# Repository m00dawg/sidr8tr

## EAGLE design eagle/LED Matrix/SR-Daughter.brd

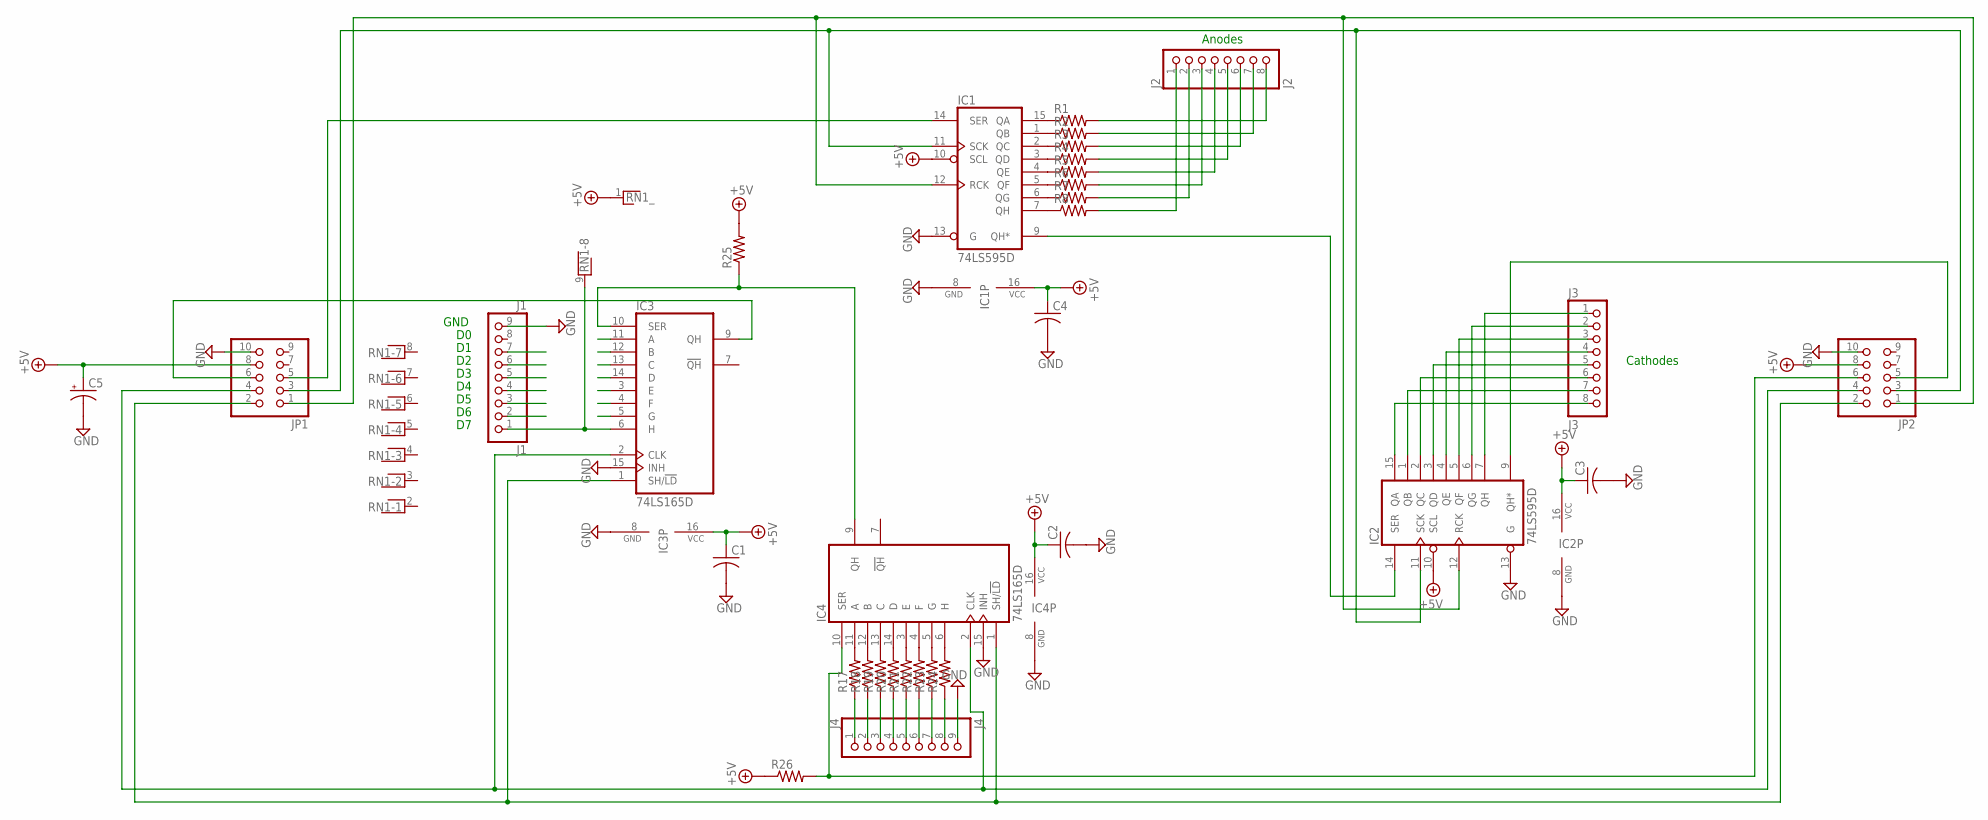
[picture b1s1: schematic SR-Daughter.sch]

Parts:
C1, C2, C3, C4: C-USC0603; C0603
C5: CPOL-USE2-5; E2-5
IC1, IC2: 74LS595D; SO16
IC3, IC4: 74LS165D; SO16
J1: J1; 1X09
J2: J2; 1X08
J3: J3; 1X08
J4: J4; 1X09
JP1, JP2: PINHD-2X5; 2X05
R1, R2, R3, R4, R5, R6, R7, R8, R17, R18, R19, R20, R21, R22, R23, R24, R25, R26: R-US_M0805; M0805
RN1: RNX8; RN-9

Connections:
+5V: C1.1, C2.1, C3.1, C4.1, C5.+, IC1.10 (SCL), IC1.16 (VCC), IC2.10 (SCL), IC2.16 (VCC), IC3.16 (VCC), IC4.16 (VCC), JP1.8, JP2.8, R25.2, R26.1, RN1.1
CLK0: IC3.2 (CLK), IC4.2 (CLK), JP1.4, JP2.4
CLK1: IC3.1 (SH/!LD), IC4.1 (SH/!LD), JP1.2, JP2.2
GND: C1.2, C2.2, C3.2, C4.2, C5.-, IC1.8 (GND), IC1.13 (G), IC2.8 (GND), IC2.13 (G), IC3.8 (GND), IC3.15 (INH), IC4.8 (GND), IC4.15 (INH), J1.9, J4.9, JP1.10, JP2.10
unnamed: IC1.15 (QA), R1.1
unnamed: IC1.1 (QB), R2.1
unnamed: IC1.2 (QC), R3.1
unnamed: IC1.3 (QD), R4.1
unnamed: IC1.4 (QE), R5.1
unnamed: IC1.5 (QF), R6.1
unnamed: IC1.6 (QG), R7.1
unnamed: IC1.7 (QH), R8.1
unnamed: J2.1, R8.2
unnamed: J2.2, R7.2
unnamed: J2.3, R6.2
unnamed: J2.4, R5.2
unnamed: J2.5, R4.2
unnamed: J2.6, R3.2
unnamed: J2.7, R2.2
unnamed: IC3.6 (H), J1.1, RN1.9
unnamed: IC4.11 (A), R17.2
unnamed: IC4.12 (B), R18.2
unnamed: J2.8, R1.2
unnamed: IC2.15 (QA), J3.8
unnamed: IC2.1 (QB), J3.7
unnamed: IC2.2 (QC), J3.6
unnamed: IC2.3 (QD), J3.5
unnamed: IC2.4 (QE), J3.4
unnamed: IC4.13 (C), R19.2
unnamed: IC4.14 (D), R20.2
unnamed: IC2.5 (QF), J3.3
unnamed: IC4.3 (E), R21.2
unnamed: IC4.4 (F), R22.2
unnamed: IC4.5 (G), R23.2
unnamed: IC2.6 (QG), J3.2
unnamed: IC2.7 (QH), J3.1
unnamed: J4.1, R17.1
unnamed: J4.2, R18.1
unnamed: J4.3, R19.1
unnamed: J4.4, R20.1
unnamed: J4.5, R21.1
unnamed: J4.6, R22.1
unnamed: J4.7, R23.1
unnamed: IC4.6 (H), R24.2
unnamed: J4.8, R24.1
unnamed: IC3.9 (QH), JP1.6
unnamed: IC3.10 (SER), IC4.9 (QH), R25.1
unnamed: IC4.10 (SER), JP2.6, R26.2
unnamed: IC1.14 (SER), JP1.5
unnamed: IC1.9 (QH*), IC2.14 (SER)
unnamed: IC2.9 (QH*), JP2.5
unnamed: IC1.12 (RCK), IC2.12 (RCK), JP1.1, JP2.1
unnamed: IC1.11 (SCK), IC2.11 (SCK), JP1.3, JP2.3

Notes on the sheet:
GND
Anodes
Cathodes

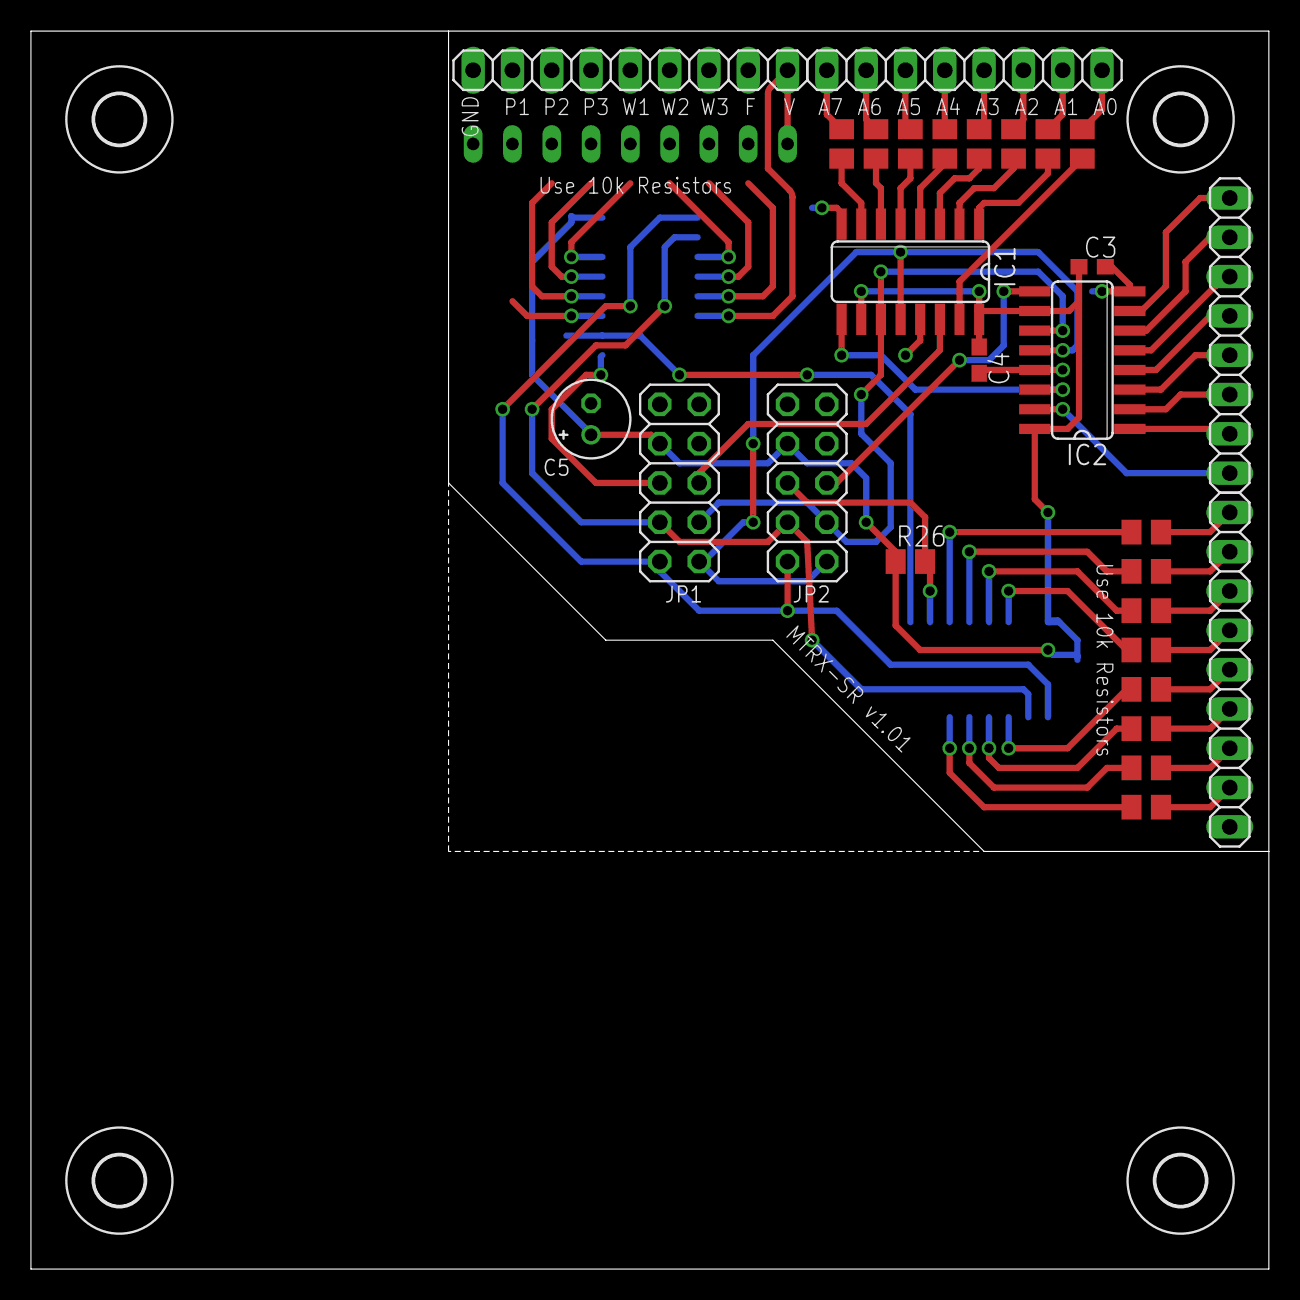
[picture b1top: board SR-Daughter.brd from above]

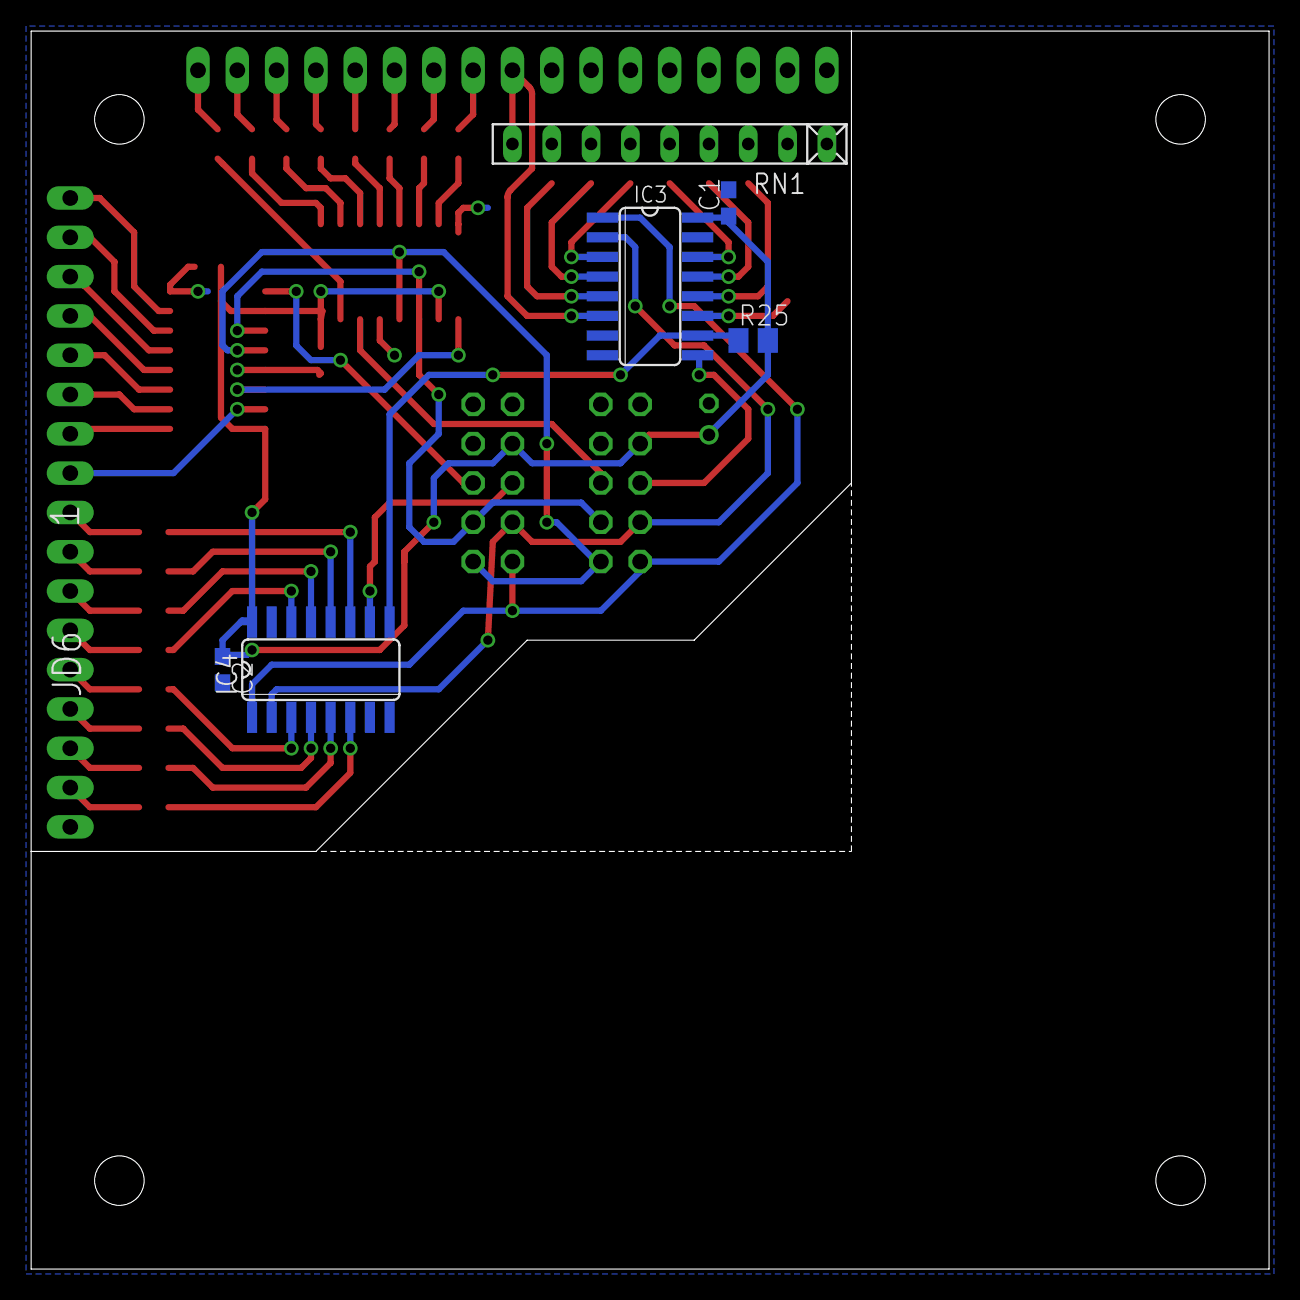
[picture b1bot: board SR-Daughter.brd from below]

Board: 2 copper layers, 80.0 x 80.0 mm, 38 parts (6 on the bottom side), 53 nets.

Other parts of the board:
U$1, U$2, U$3, U$4: 3,2
